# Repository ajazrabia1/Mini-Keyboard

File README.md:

Marcropad. 
4 key macropad from scratch using kicad and fusion. The hackpad project was coded in python . Keys are for easy copy and pasting as well as an undo key and a key to switch tabs!

A screenshot of the macropad design

A screenshot of the schematic:

A screenshot of the PCB layout:

A screenshot of the case in 3D

A bill of materials listing every component:

 XIAO RP2040
 4 MX switches
 4 keycaps
 PCB fabricated
 3D printed bottom case
 3D printed plate
 4× M3 screws
 4× M3 nuts
 USB-C cable

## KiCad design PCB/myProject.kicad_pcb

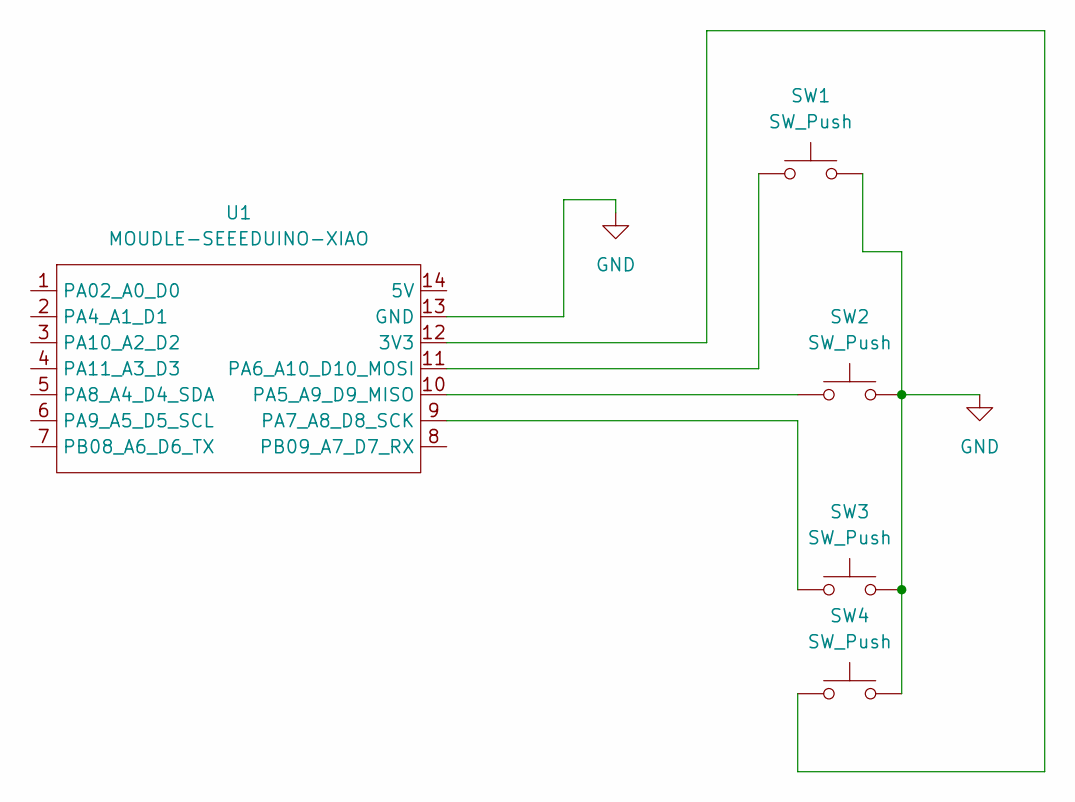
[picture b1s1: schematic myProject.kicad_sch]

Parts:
SW1, SW2, SW3, SW4: SW_Push; SW_Cherry_MX_1.00u_PCB
U1: MOUDLE-SEEEDUINO-XIAO; XIAO-Generic-Hybrid-14P-2.54-21X17.8MM

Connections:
GND: SW1.2, SW2.2, SW3.2, SW4.2, U1.13 (GND)
unnamed: SW4.1, U1.12 (3V3)
unnamed: SW2.1, U1.10 (PA5_A9_D9_MISO)
unnamed: SW1.1, U1.11 (PA6_A10_D10_MOSI)
unnamed: SW3.1, U1.9 (PA7_A8_D8_SCK)

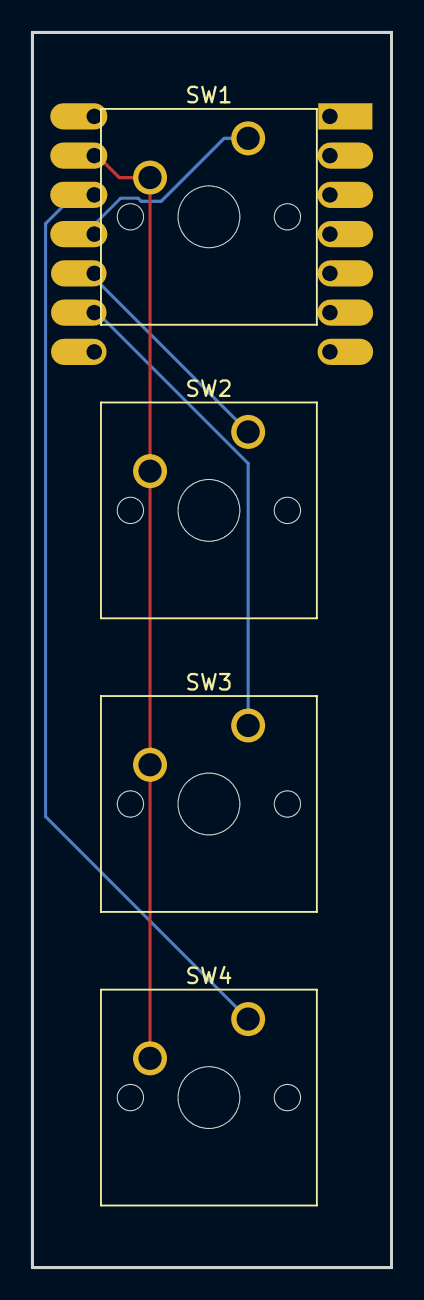
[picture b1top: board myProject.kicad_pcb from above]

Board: 2 copper layers, 23.2 x 79.9 mm, 5 parts (1 on the bottom side), 5 nets.
